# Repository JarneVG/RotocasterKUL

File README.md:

# RotocasterKUL
This is the accompanying report and documentation for the rotocasting machine, made in 2025 for the KU Leuven soft robotics research team.

## Software
Here, you can find the main code under RotocasterMainFirmware (arduino .ino files) as well as other people's libraries used for this project.

I changed some of these libraries to add or change functionalities, so be sure to add the ones you find here to your Arduino -> libraries directory

You should also have the Earle Philhowers Arduino Pico core installed.

Some useful tutorials for uploading:

https://learn.adafruit.com/rp2040-arduino-with-the-earlephilhower-core/installing-the-earlephilhower-core

https://randomnerdtutorials.com/programming-raspberry-pi-pico-w-arduino-ide/

## Electrical Hardware
The KiCAD design files can be found here. If there is something that needs to change, you can find the current version of the project here. The small problems with the current version are already implemented.

## Mechanical Hardware
A .step file is uploaded here to get a better grasp of what might be going on under the covers. This is not a build guide, rather part of the documentation.
Same thing for the bill of materials, where you can find all the parts used in this project

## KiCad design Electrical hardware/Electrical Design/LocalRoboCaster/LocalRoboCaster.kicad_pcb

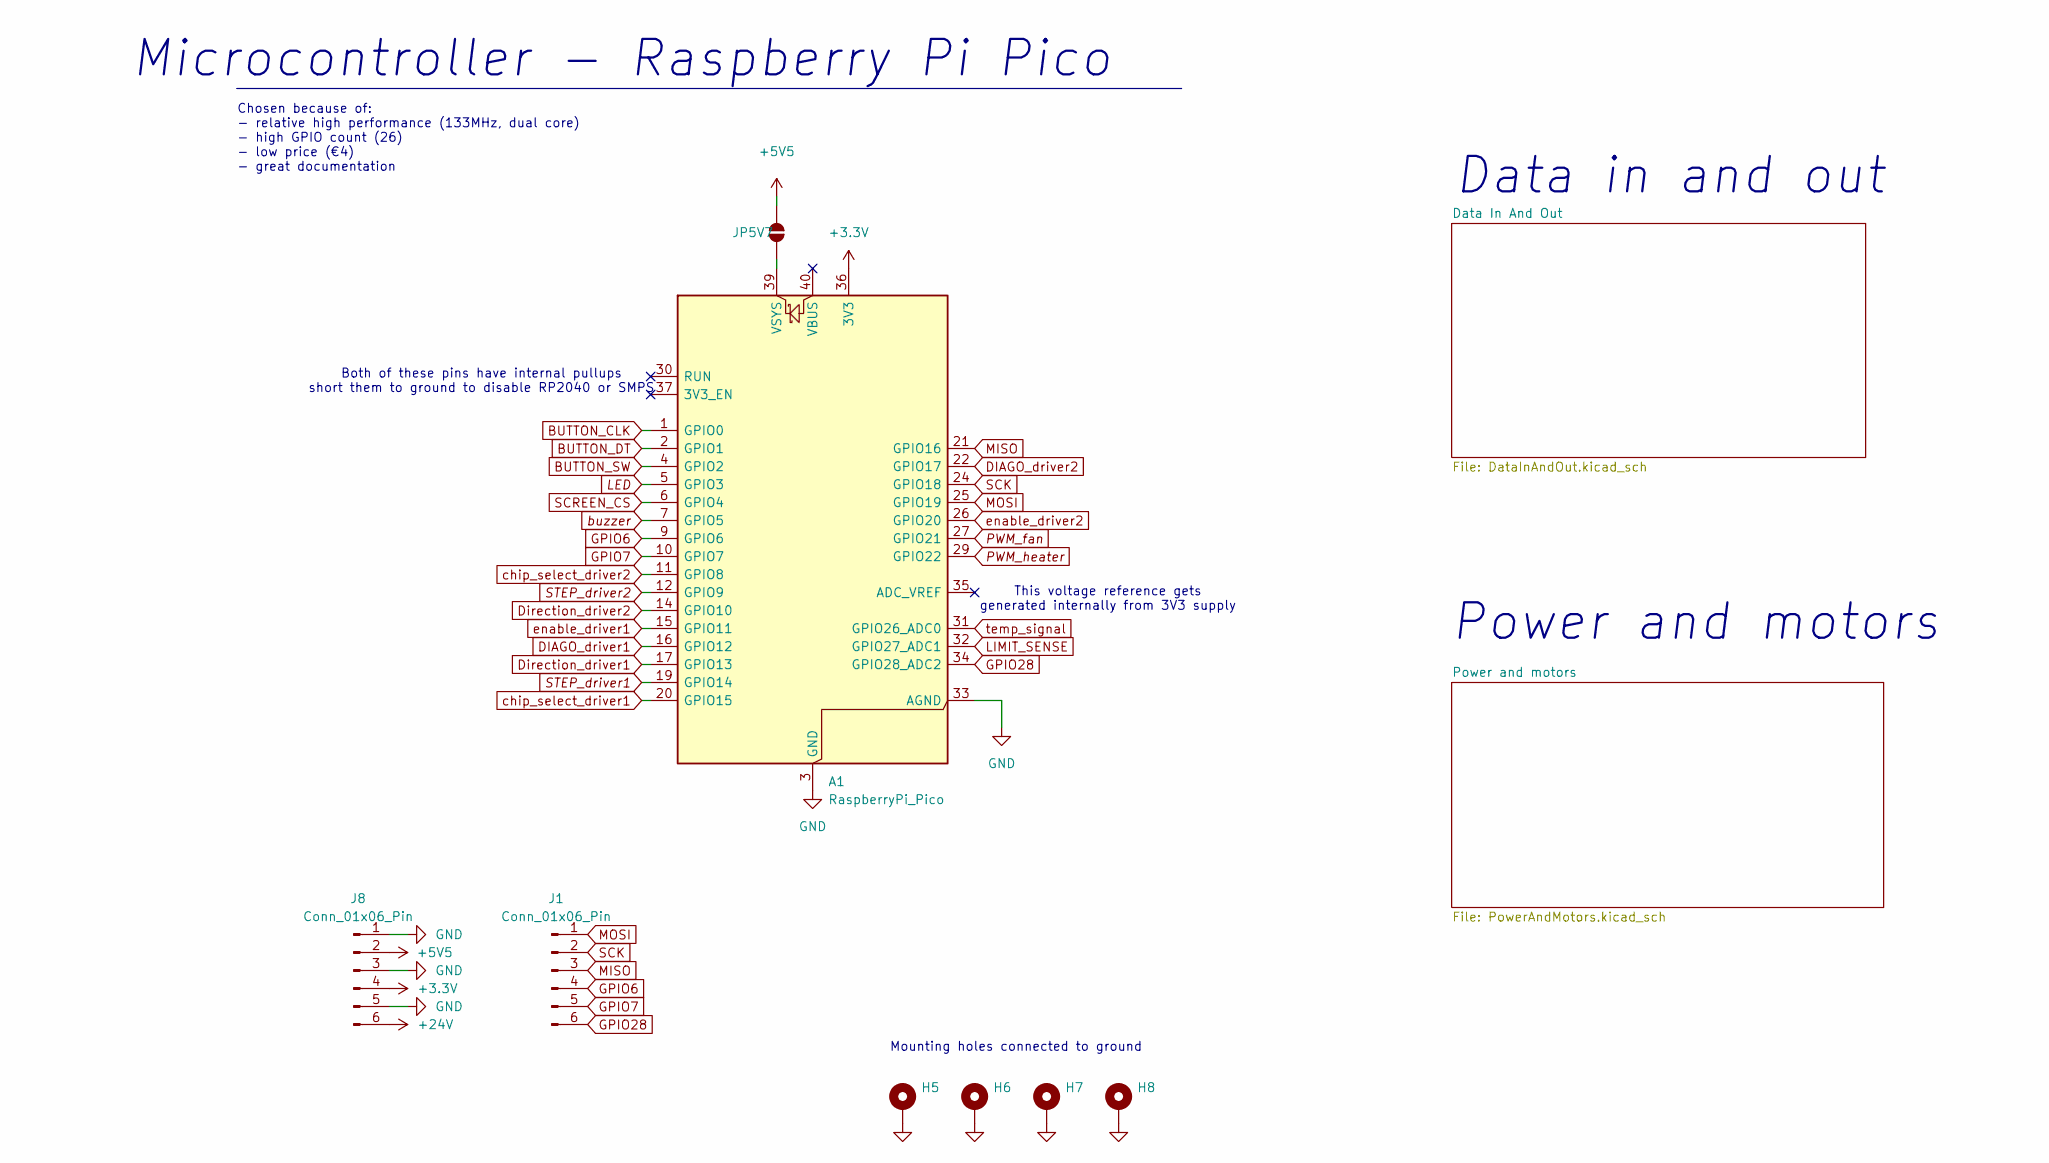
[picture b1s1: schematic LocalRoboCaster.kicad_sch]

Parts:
A1: RaspberryPi_Pico; Pico
H5, H6, H7, H8: GND; MountingHole_3.2mm_M3_Pad_Via
J1, J8: Conn_01x06_Pin; PinHeader_1x06_P2.54mm_Vertical
JP5V7: SolderJumper_2_Open; SolderJumper-2_P1.3mm_Open_RoundedPad1.0x1.5mm

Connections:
+3.3V: A1.36 (3V3), J8.4; also elsewhere on the board
+5V5: J8.2, JP5V7.2 (B); also elsewhere on the board
+24V: J8.6; also elsewhere on the board
BUTTON_CLK: A1.1 (GPIO0); also elsewhere on the board
BUTTON_DT: A1.2 (GPIO1); also elsewhere on the board
BUTTON_SW: A1.4 (GPIO2); also elsewhere on the board
DIAGO_driver1: A1.16 (GPIO12); also elsewhere on the board
DIAGO_driver2: A1.22 (GPIO17); also elsewhere on the board
Direction_driver1: A1.17 (GPIO13); also elsewhere on the board
Direction_driver2: A1.14 (GPIO10); also elsewhere on the board
GND: A1.3 (GND), A1.8 (GND), A1.13 (GND), A1.18 (GND), A1.23 (GND), A1.28 (GND), A1.33 (AGND), A1.38 (GND), H5.1, H6.1, H7.1, H8.1, J8.1, J8.3, J8.5; also elsewhere on the board
GPIO6: A1.9 (GPIO6), J1.4
GPIO7: A1.10 (GPIO7), J1.5
GPIO28: A1.34 (GPIO28_ADC2), J1.6
LED: A1.5 (GPIO3); also elsewhere on the board
LIMIT_SENSE: A1.32 (GPIO27_ADC1); also elsewhere on the board
MISO: A1.21 (GPIO16), J1.3; also elsewhere on the board
MOSI: A1.25 (GPIO19), J1.1; also elsewhere on the board
unnamed: A1.39 (VSYS), JP5V7.1 (A)
PWM_fan: A1.27 (GPIO21); also elsewhere on the board
PWM_heater: A1.29 (GPIO22); also elsewhere on the board
SCK: A1.24 (GPIO18), J1.2; also elsewhere on the board
SCREEN_CS: A1.6 (GPIO4); also elsewhere on the board
STEP_driver1: A1.19 (GPIO14); also elsewhere on the board
STEP_driver2: A1.12 (GPIO9); also elsewhere on the board
buzzer: A1.7 (GPIO5); also elsewhere on the board
chip_select_driver1: A1.20 (GPIO15); also elsewhere on the board
chip_select_driver2: A1.11 (GPIO8); also elsewhere on the board
enable_driver1: A1.15 (GPIO11); also elsewhere on the board
enable_driver2: A1.26 (GPIO20); also elsewhere on the board
temp_signal: A1.31 (GPIO26_ADC0); also elsewhere on the board

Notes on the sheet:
Microcontroller - Raspberry Pi Pico
Chosen because of: - relative high performance (133MHz, dual core) - high GPIO count (26) - low price (€4) - great documentation
This voltage reference gets generated internally from 3V3 supply
Mounting holes connected to ground
Data in and out
Both of these pins have internal pullups short them to ground to disable RP2040 or SMPS
Power and motors

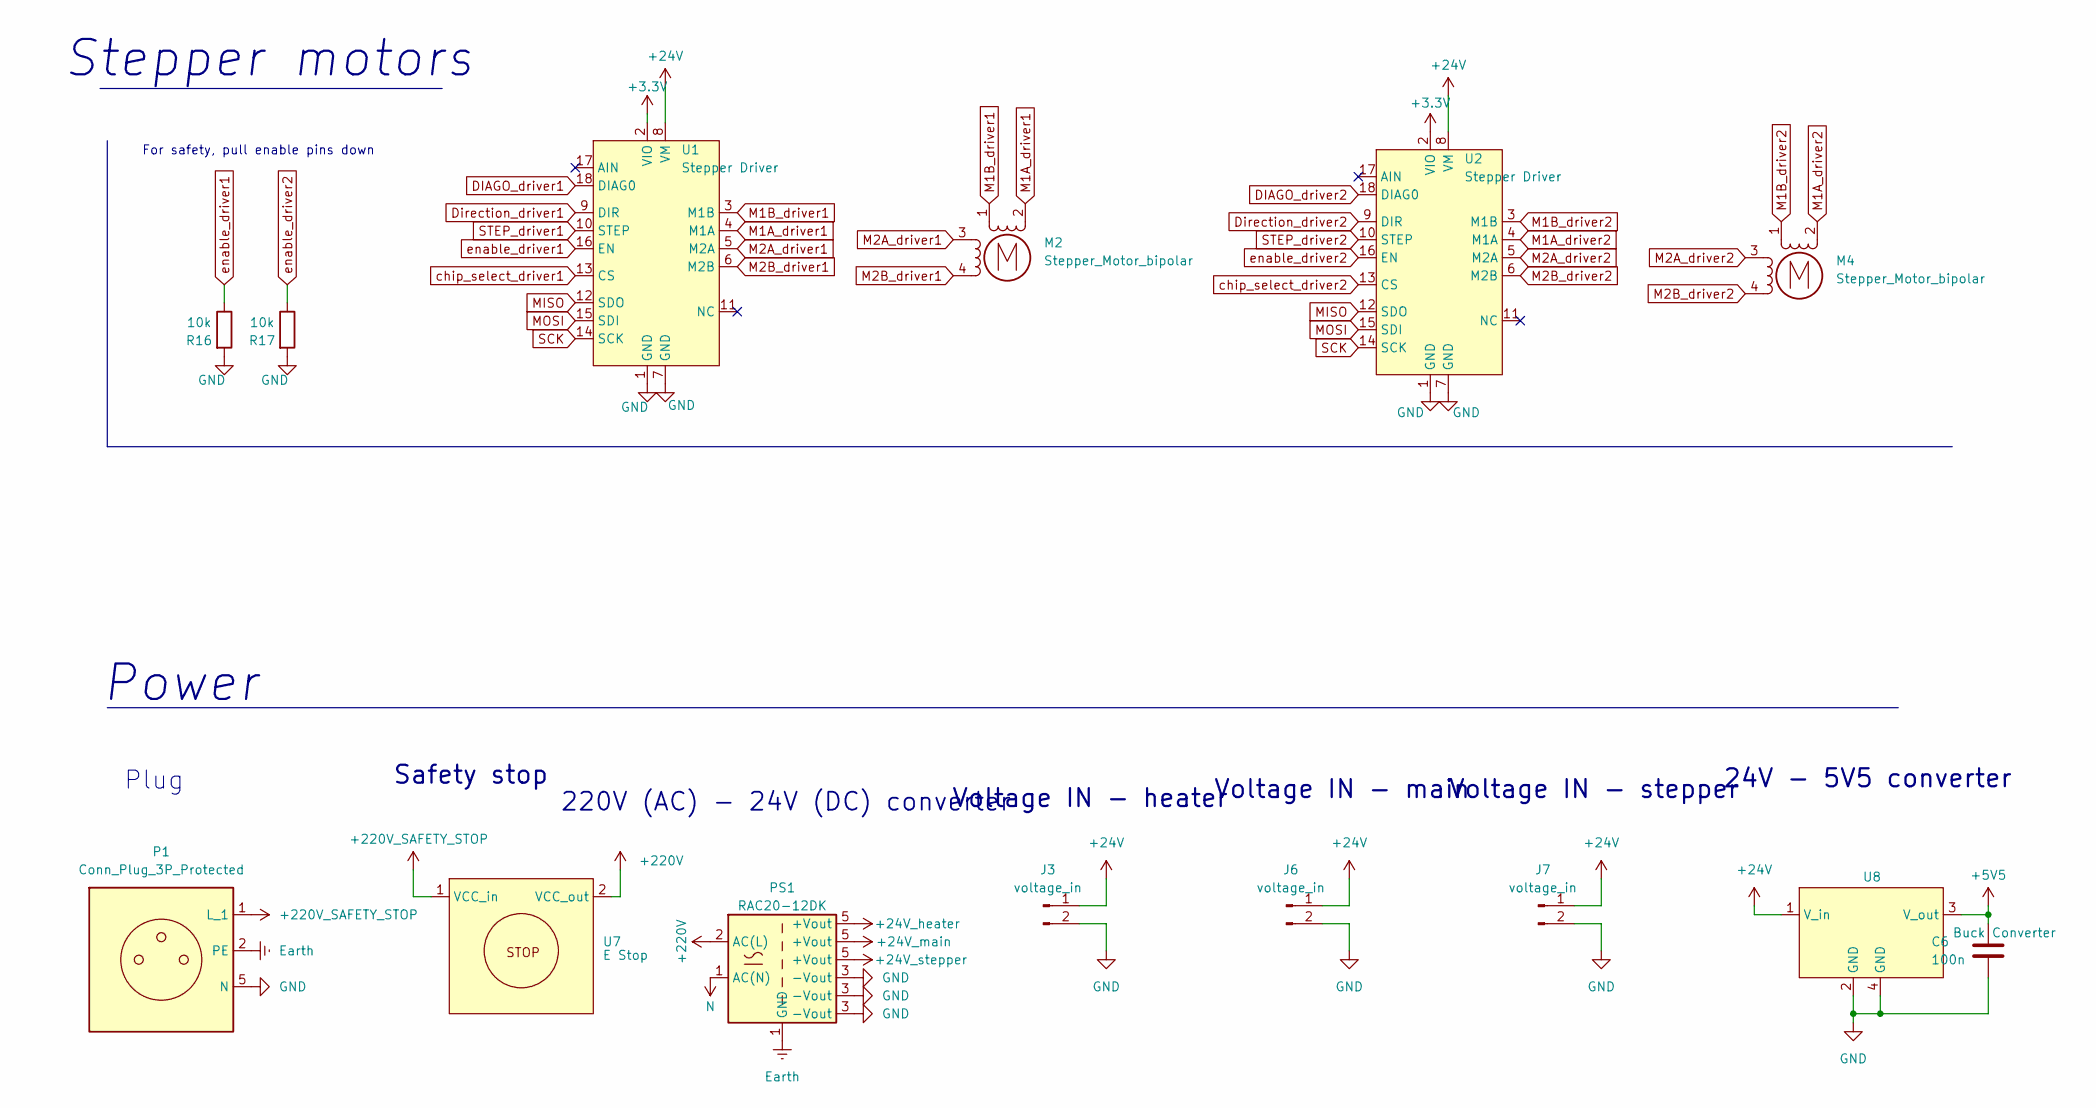
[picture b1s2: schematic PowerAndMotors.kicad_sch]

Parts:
C6: 100n; C_0603_1608Metric_Pad1.08x0.95mm_HandSolder
J3, J6, J7: voltage_in; TerminalBlock_Phoenix_MKDS-1,5-2-5.08_1x02_P5.08mm_Horizont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
M2, M4: Stepper_Motor_bipolar; JST_XH_B4B-XH-A_1x04_P2.50mm_Vertical
P1: Conn_Plug_3P_Protected
PS1: RAC20-12DK
R16, R17: 10k; R_0603_1608Metric_Pad0.98x0.95mm_HandSolder
U1, U2: Stepper Driver; Pololu_Breakout-16_15.2x20.3mm
U7: E Stop
U8: Buck Converter; LM2596

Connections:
+3.3V: U1.2 (VIO), U2.2 (VIO); also elsewhere on the board
+5V5: C6.1, U8.3 (V_out); also elsewhere on the board
+24V: J3.1, J6.1, J7.1, U1.8 (VM), U2.8 (VM), U8.1 (V_in); also elsewhere on the board
DIAGO_driver1: U1.18 (DIAG0); also elsewhere on the board
DIAGO_driver2: U2.18 (DIAG0); also elsewhere on the board
Direction_driver1: U1.9 (DIR); also elsewhere on the board
Direction_driver2: U2.9 (DIR); also elsewhere on the board
GND: C6.2, J3.2, J6.2, J7.2, P1.5 (N), PS1.3 (-Vout), R16.2, R17.2, U1.1 (GND), U1.7 (GND), U2.1 (GND), U2.7 (GND), U8.2 (GND), U8.4 (GND); also elsewhere on the board
M1A_driver1: M2.2 (-), U1.4 (M1A)
M1A_driver2: M4.2 (-), U2.4 (M1A)
M1B_driver1: M2.1, U1.3 (M1B)
M1B_driver2: M4.1, U2.3 (M1B)
M2A_driver1: M2.3, U1.5 (M2A)
M2A_driver2: M4.3, U2.5 (M2A)
M2B_driver1: M2.4, U1.6 (M2B)
M2B_driver2: M4.4, U2.6 (M2B)
MISO: U1.12 (SDO), U2.12 (SDO); also elsewhere on the board
MOSI: U1.15 (SDI), U2.15 (SDI); also elsewhere on the board
unnamed: P1.1 (L_1), U7.1 (VCC_in)
unnamed: P1.2 (PE), PS1.1 (AC(N))
unnamed: PS1.2 (AC(L)), U7.2 (VCC_out)
SCK: U1.14 (SCK), U2.14 (SCK); also elsewhere on the board
STEP_driver1: U1.10 (STEP); also elsewhere on the board
STEP_driver2: U2.10 (STEP); also elsewhere on the board
chip_select_driver1: U1.13 (CS); also elsewhere on the board
chip_select_driver2: U2.13 (CS); also elsewhere on the board
enable_driver1: R16.1, U1.16 (EN); also elsewhere on the board
enable_driver2: R17.1, U2.16 (EN); also elsewhere on the board

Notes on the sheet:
Plug
Voltage IN - main
Stepper motors
24V - 5V5 converter
Voltage IN - heater
For safety, pull enable pins down
220V (AC) - 24V (DC) converter
Power
Voltage IN - stepper
Safety stop

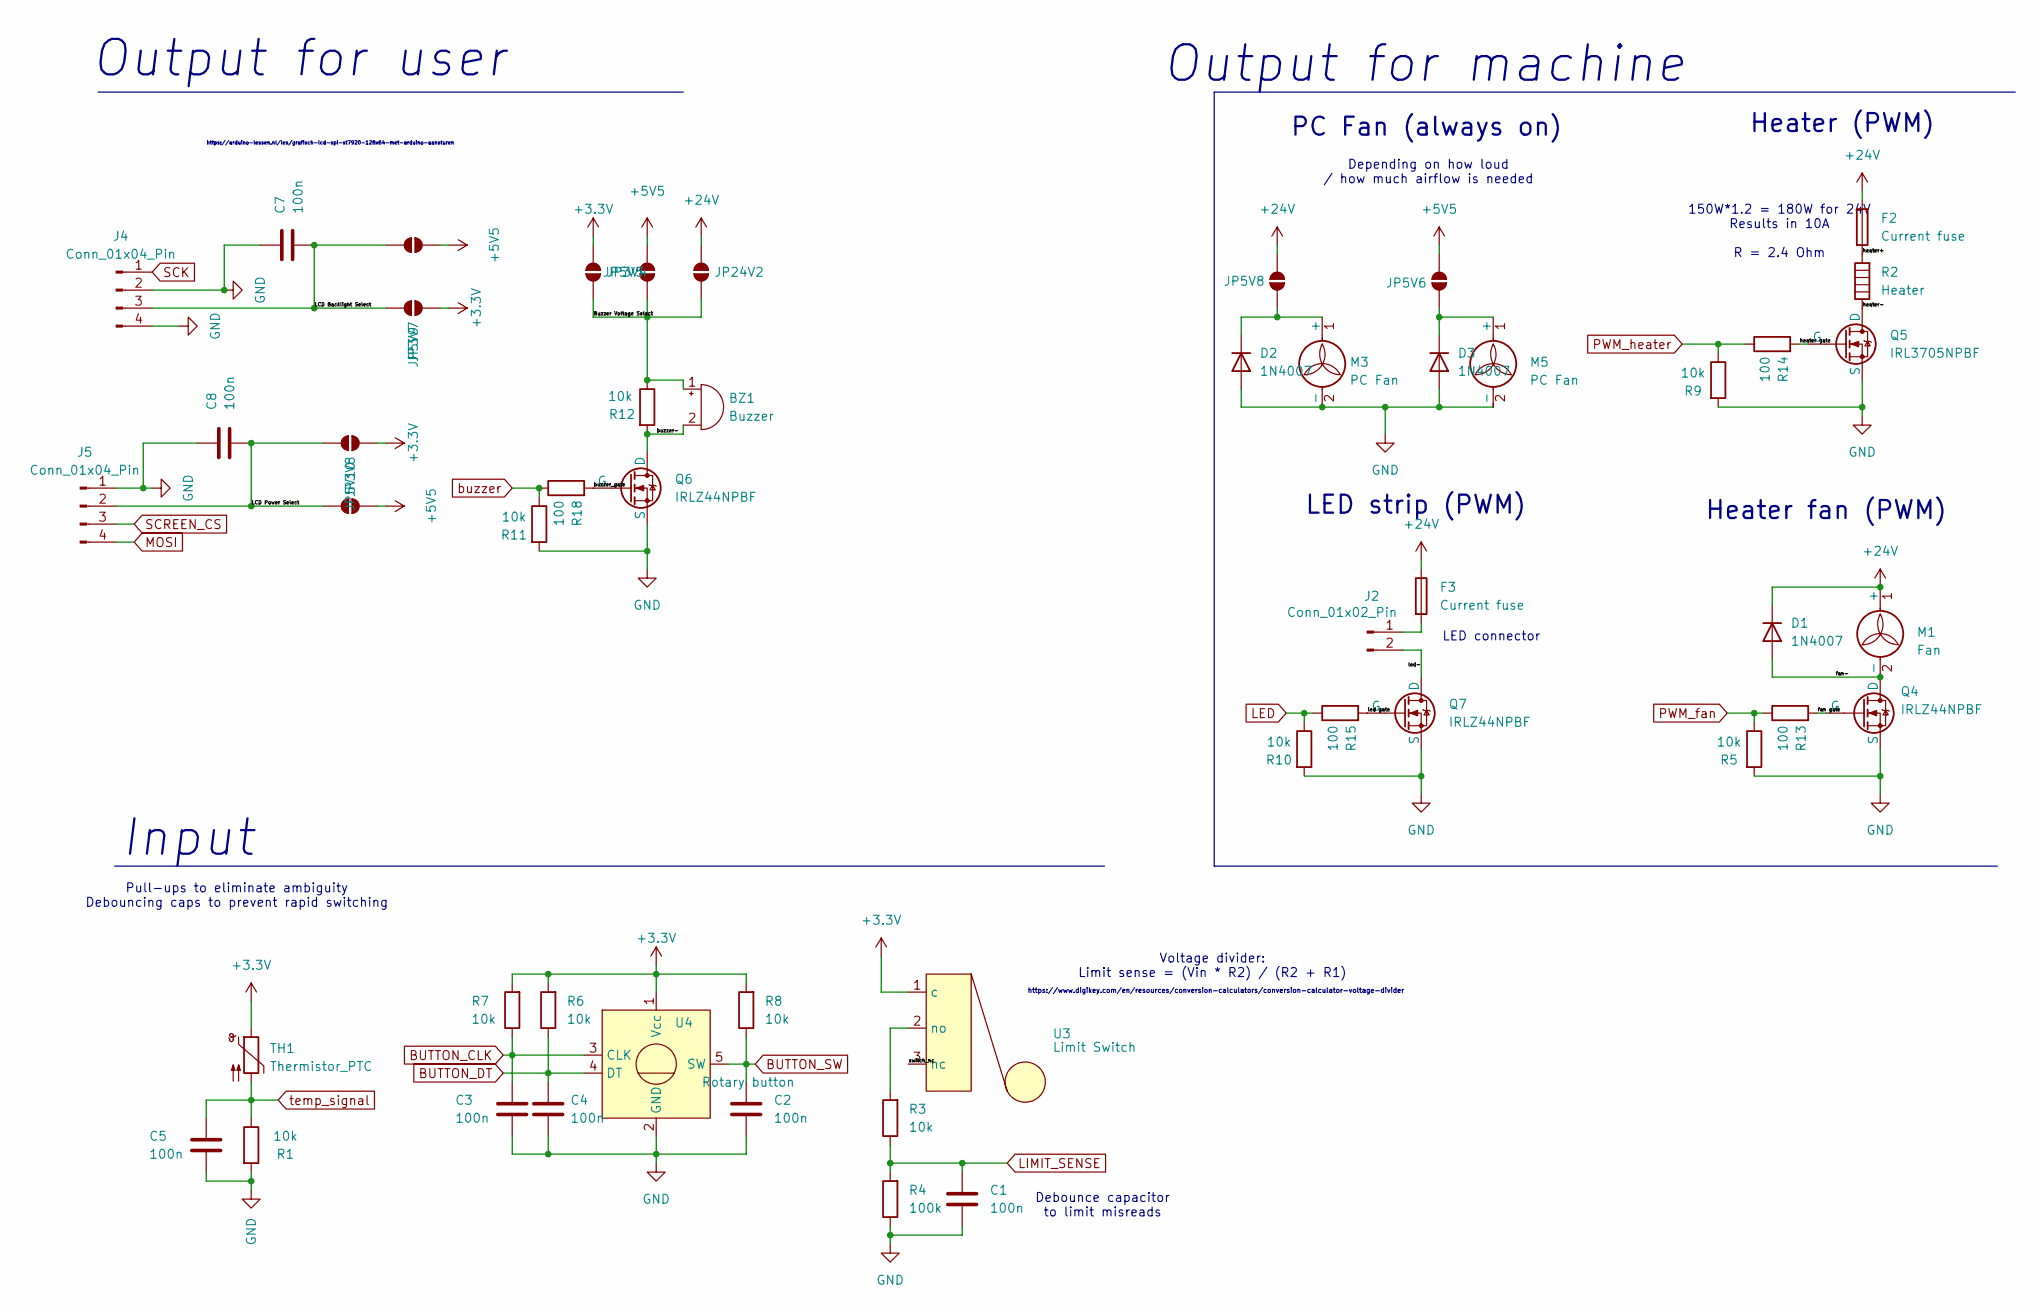
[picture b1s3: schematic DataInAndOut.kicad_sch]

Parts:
BZ1: Buzzer; Buzzer_12x9.5RM7.6
C1, C2, C3, C4, C5, C7, C8: 100n; C_0603_1608Metric_Pad1.08x0.95mm_HandSolder
D1, D2, D3: 1N4007; D_DO-41_SOD81_P10.16mm_Horizontal
F2: Current fuse; Fuse Holder RS Pro Fuse Blade
F3: Current fuse; Fuse_Bourns_MF-RHT1000
J2: Conn_01x02_Pin; TerminalBlock_Phoenix_MKDS-1,5-2-5.08_1x02_P5.08mm_Horizont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
J4, J5: Conn_01x04_Pin; JST_XH_B4B-XH-A_1x04_P2.50mm_Vertical
JP3V4, JP3V7, JP3V8, JP5V5, JP5V6, JP5V8, JP5V9, JP5V10, JP24V2: SolderJumper_2_Open; SolderJumper-2_P1.3mm_Open_RoundedPad1.0x1.5mm
M1: Fan; TerminalBlock_Phoenix_MKDS-1,5-2-5.08_1x02_P5.08mm_Horizont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
M3, M5: PC Fan; PinHeader_1x02_P2.54mm_Vertical
Q4, Q6, Q7: IRLZ44NPBF; TO-220F-3_Vertical
Q5: IRL3705NPBF; TO-220F-3_Vertical
R1, R3, R5, R6, R7, R8, R9, R10, R11, R12: 10k; R_0603_1608Metric_Pad0.98x0.95mm_HandSolder
R2: Heater; TerminalBlock_Phoenix_MKDS-1,5-2-5.08_1x02_P5.08mm_Horizont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
R4: 100k; R_0603_1608Metric_Pad0.98x0.95mm_HandSolder
R13, R14, R15, R18: 100; R_0603_1608Metric_Pad0.98x0.95mm_HandSolder
TH1: Thermistor_PTC; JST_XH_B2B-XH-A_1x02_P2.50mm_Vertical
U3: Limit Switch; JST_XH_B2B-XH-A_1x02_P2.50mm_Vertical
U4: Rotary button; JST_XH_B5B-XH-A_1x05_P2.50mm_Vertical

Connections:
+3.3V: JP3V4.2 (B), JP3V7.2 (B), JP3V8.2 (B), R6.2, R7.2, R8.2, TH1.1, U3.1 (c), U4.1 (Vcc); also elsewhere on the board
+5V5: JP5V5.2 (B), JP5V6.2 (B), JP5V9.2 (B), JP5V10.2 (B); also elsewhere on the board
+24V: D1.1 (K), F2.1, F3.1, JP5V8.2 (B), JP24V2.2 (B), M1.1 (+); also elsewhere on the board
/Data In And Out/Buzzer Voltage Select: BZ1.1 (+), JP3V4.1 (A), JP5V5.1 (A), JP24V2.1 (A), R12.1
/Data In And Out/LCD Backlight Select: C7.2, J4.3, JP3V7.1 (A), JP5V9.1 (A)
/Data In And Out/LCD Power Select: C8.2, J5.2, JP3V8.1 (A), JP5V10.1 (A)
/Data In And Out/buzzer-: BZ1.2 (-), Q6.1 (D), R12.2
/Data In And Out/buzzer_gate: Q6.2 (G), R18.2
/Data In And Out/fan gate: Q4.2 (G), R13.2
/Data In And Out/fan-: D1.2 (A), M1.2 (-), Q4.1 (D)
/Data In And Out/heater gate: Q5.2 (G), R14.2
/Data In And Out/heater+: F2.2, R2.2
/Data In And Out/heater-: Q5.1 (D), R2.1
/Data In And Out/led gate: Q7.2 (G), R15.2
/Data In And Out/led-: J2.2, Q7.1 (D)
BUTTON_CLK: C3.1, R7.1, U4.3 (CLK); also elsewhere on the board
BUTTON_DT: C4.1, R6.1, U4.4 (DT); also elsewhere on the board
BUTTON_SW: C2.1, R8.1, U4.5 (SW); also elsewhere on the board
GND: C1.2, C2.2, C3.2, C4.2, C5.2, C7.1, C8.1, D2.2 (A), D3.2 (A), J4.2, J4.4, J5.1, M3.2 (-), M5.2 (-), Q4.3 (S), Q5.3 (S), Q6.3 (S), Q7.3 (S), R1.2, R4.1, R5.2, R9.2, R10.2, R11.2, U4.2 (GND); also elsewhere on the board
LED: R10.1, R15.1; also elsewhere on the board
LIMIT_SENSE: C1.1, R3.1, R4.2; also elsewhere on the board
MOSI: J5.4; also elsewhere on the board
unnamed: D2.1 (K), JP5V8.1 (A), M3.1 (+)
unnamed: D3.1 (K), JP5V6.1 (A), M5.1 (+)
unnamed: F3.2, J2.1
unnamed: R3.2, U3.2 (no)
PWM_fan: R5.1, R13.1; also elsewhere on the board
PWM_heater: R9.1, R14.1; also elsewhere on the board
SCK: J4.1; also elsewhere on the board
SCREEN_CS: J5.3; also elsewhere on the board
buzzer: R11.1, R18.1; also elsewhere on the board
temp_signal: C5.1, R1.1, TH1.2; also elsewhere on the board

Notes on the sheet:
PC Fan (always on)
Depending on how loud / how much airflow is needed
Heater (PWM)
https://arduino-lessen.nl/les/grafisch-lcd-spi-st7920-128x64-met-arduino-aansturen
Pull-ups to eliminate ambiguity Debouncing caps to prevent rapid switching
Heater fan (PWM)
LED strip (PWM)
Input
Output for user
150W*1.2 = 180W for 24V Results in 10A R = 2.4 Ohm
Output for machine
LED connector
Debounce capacitor to limit misreads
https://www.digikey.com/en/resources/conversion-calculators/conversion-calculator-voltage-divider
Voltage divider: Limit sense = (Vin * R2) / (R2 + R1)

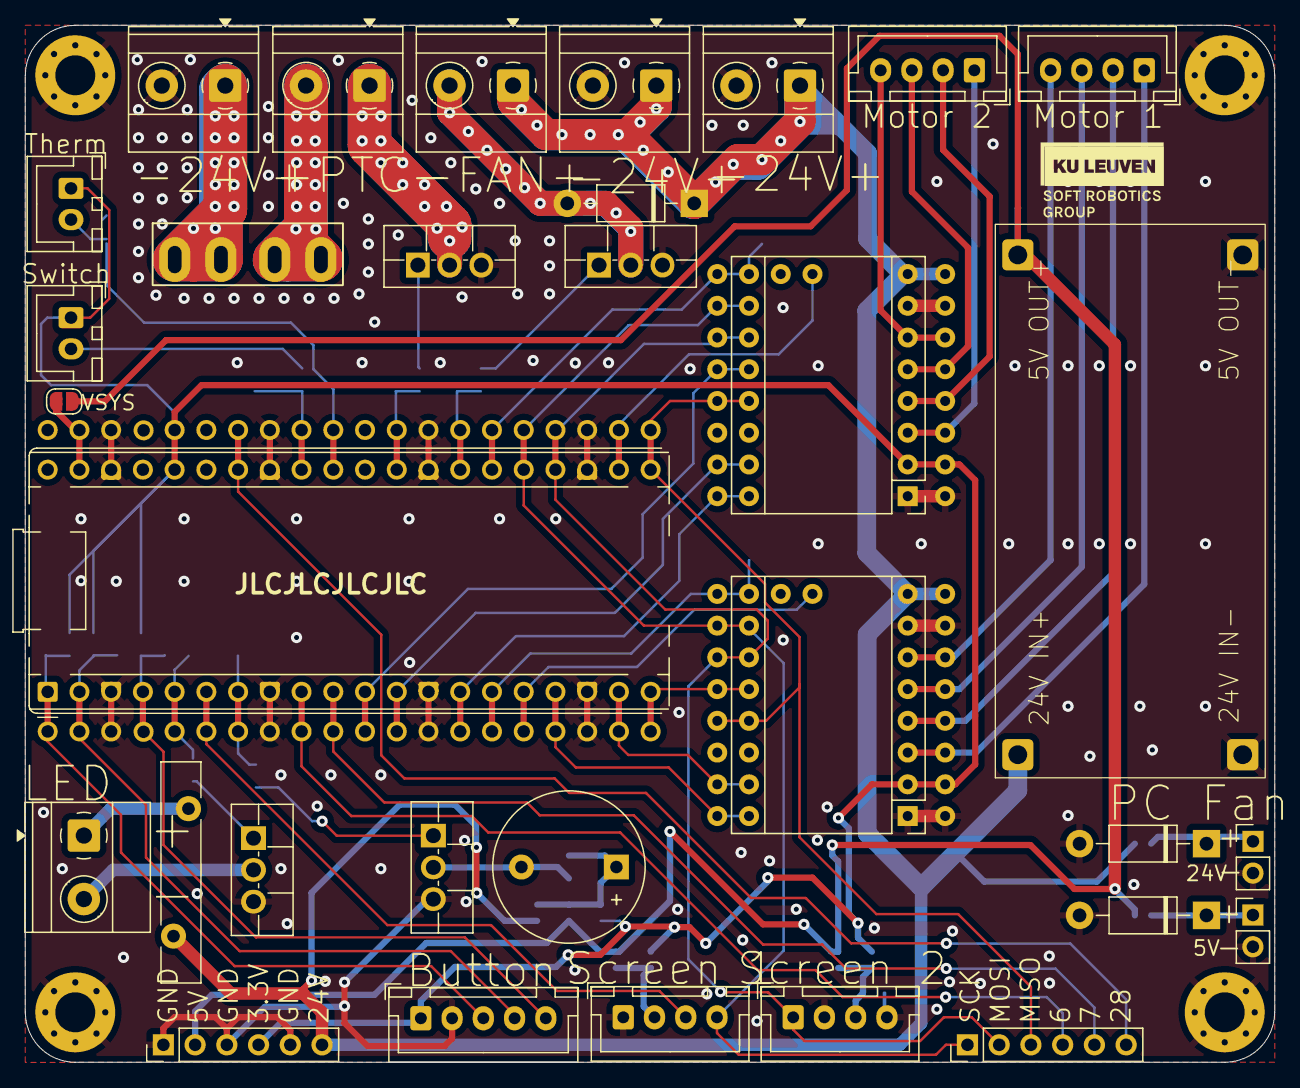
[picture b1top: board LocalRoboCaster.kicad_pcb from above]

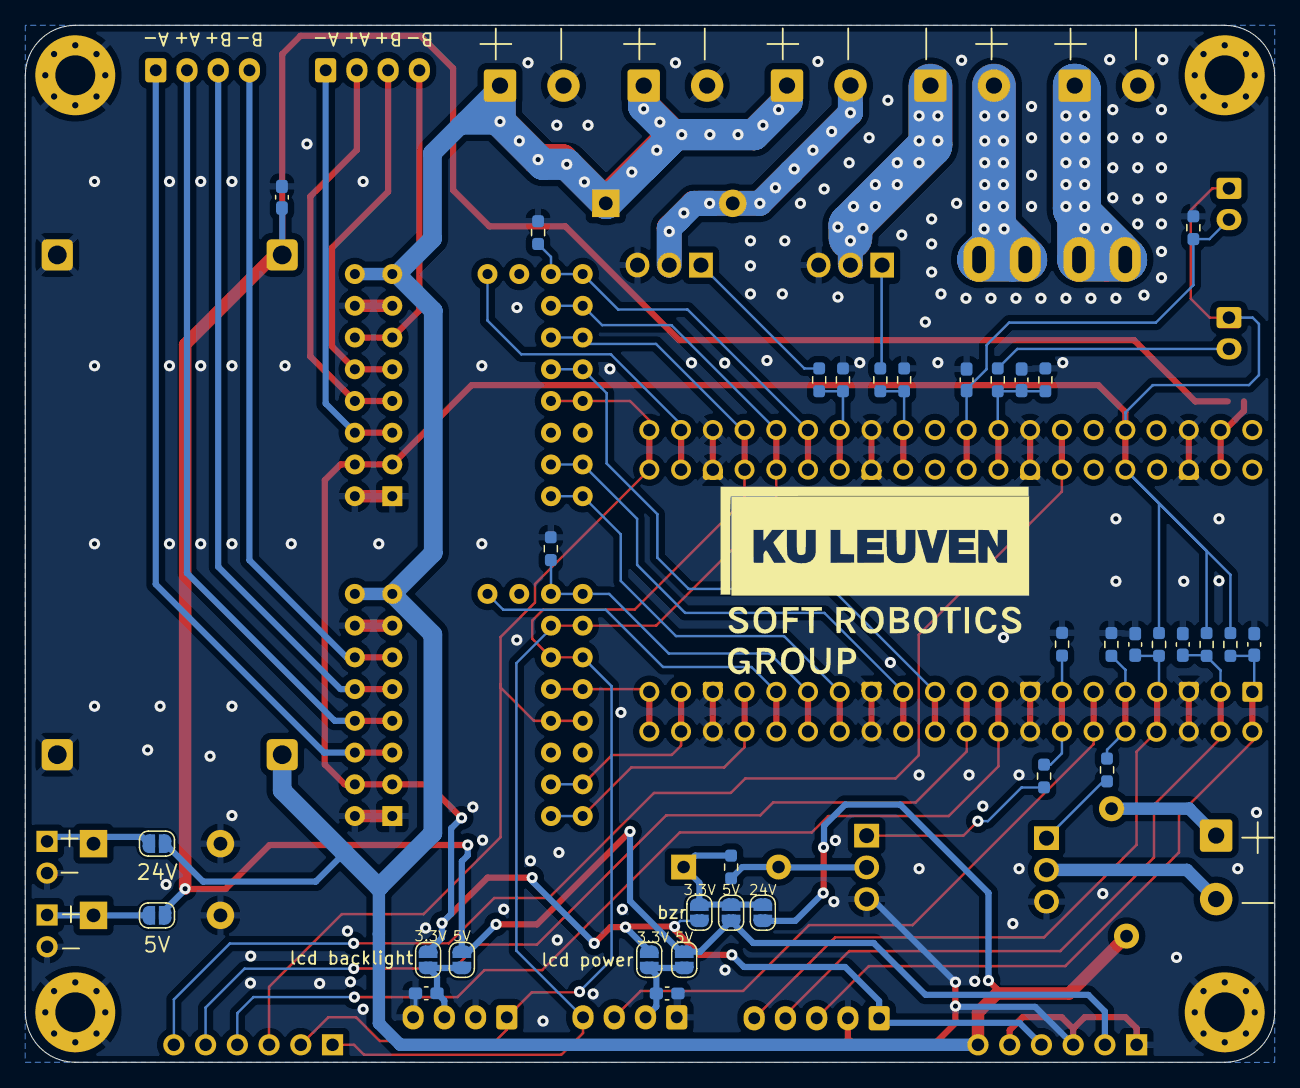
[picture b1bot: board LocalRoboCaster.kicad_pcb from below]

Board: 2 copper layers, 100.0 x 83.0 mm, 70 parts (34 on the bottom side), 55 nets.

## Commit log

2025-05-20 Added Arduino code
2025-05-20 Added 4/5 libraries
2025-05-20 Organized libraries into library folder
2025-05-20 Added hardware documentation
2025-05-20 Update README.md to include hardware sections
2025-05-20 Moved Software together in one folder
2025-05-20 Added a guide for installing pico core
2025-05-20 Added spacings
2025-05-20 Added a second guide
2025-05-21 Fixed some bugs in main software
2025-05-21 Added original repository link
2025-05-22 Added BOM in mechanical folder
2025-05-22 Added BOM description
2025-05-22 Added report and improved electrical design files
2025-05-22 Described new electrical design files
